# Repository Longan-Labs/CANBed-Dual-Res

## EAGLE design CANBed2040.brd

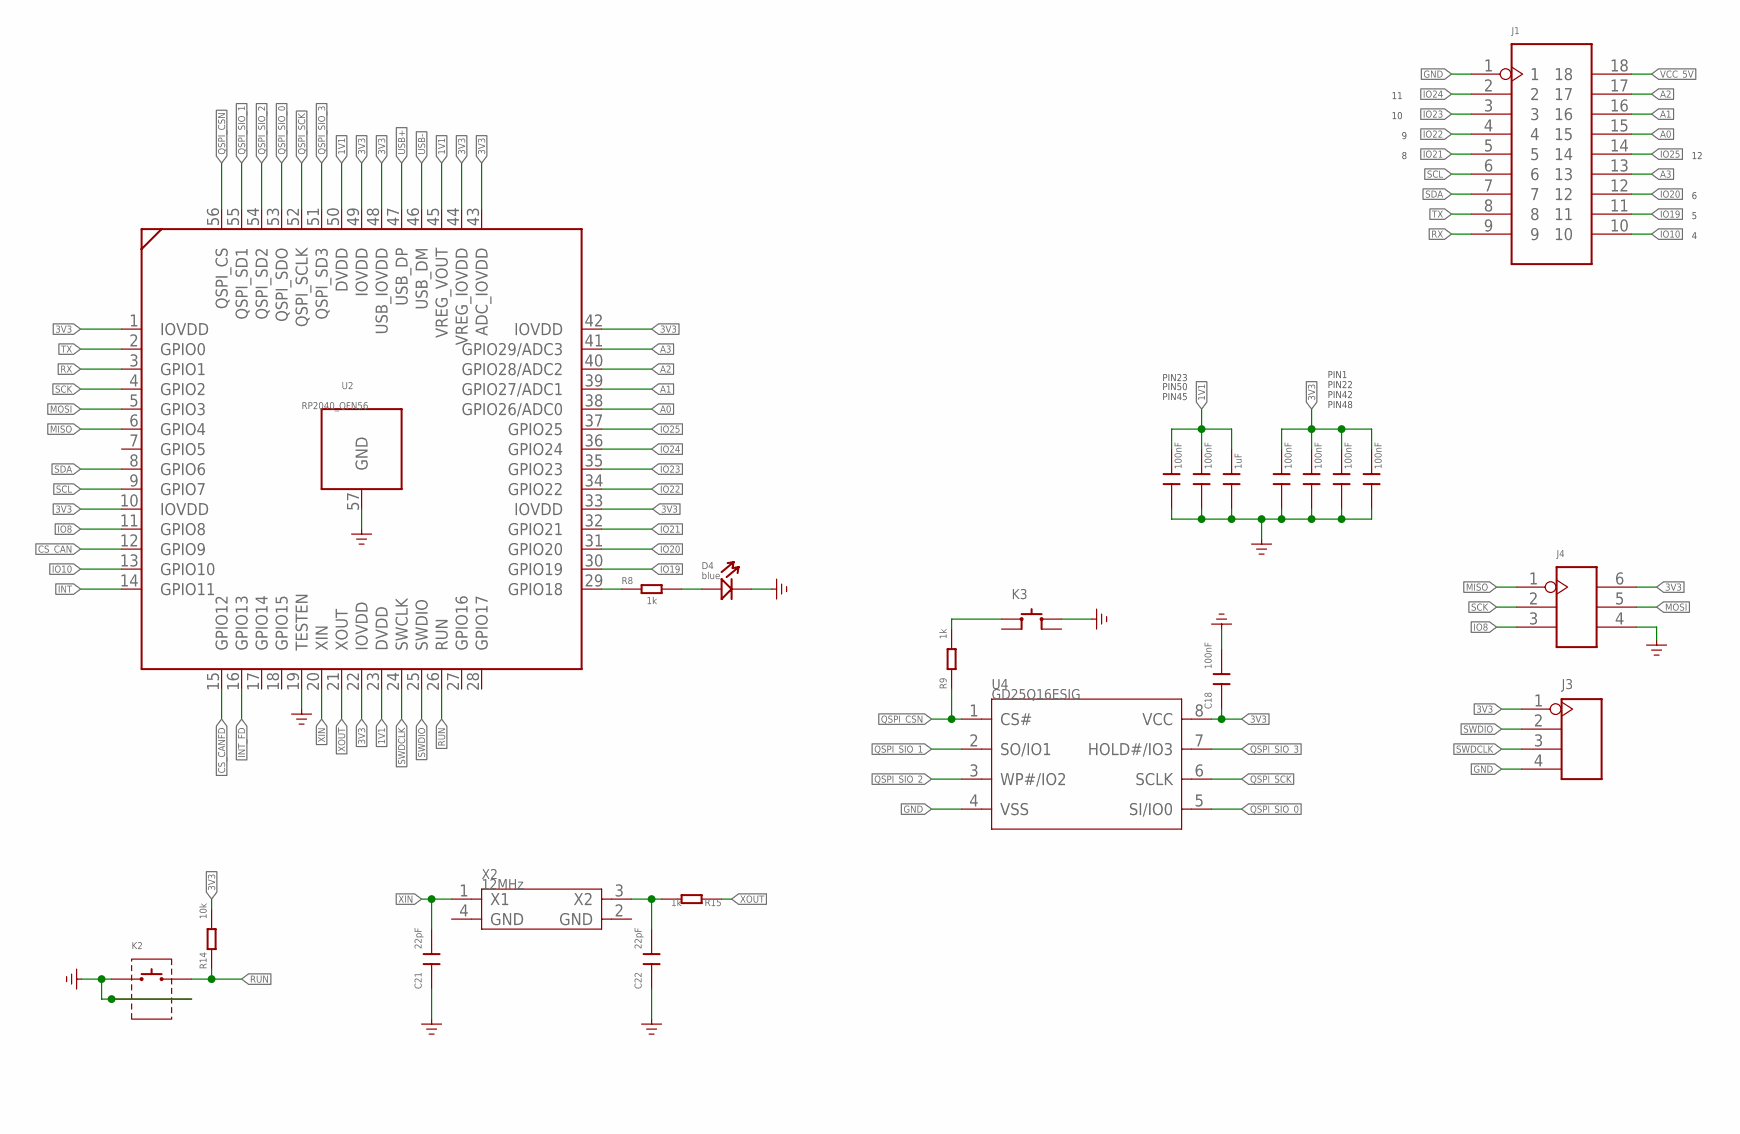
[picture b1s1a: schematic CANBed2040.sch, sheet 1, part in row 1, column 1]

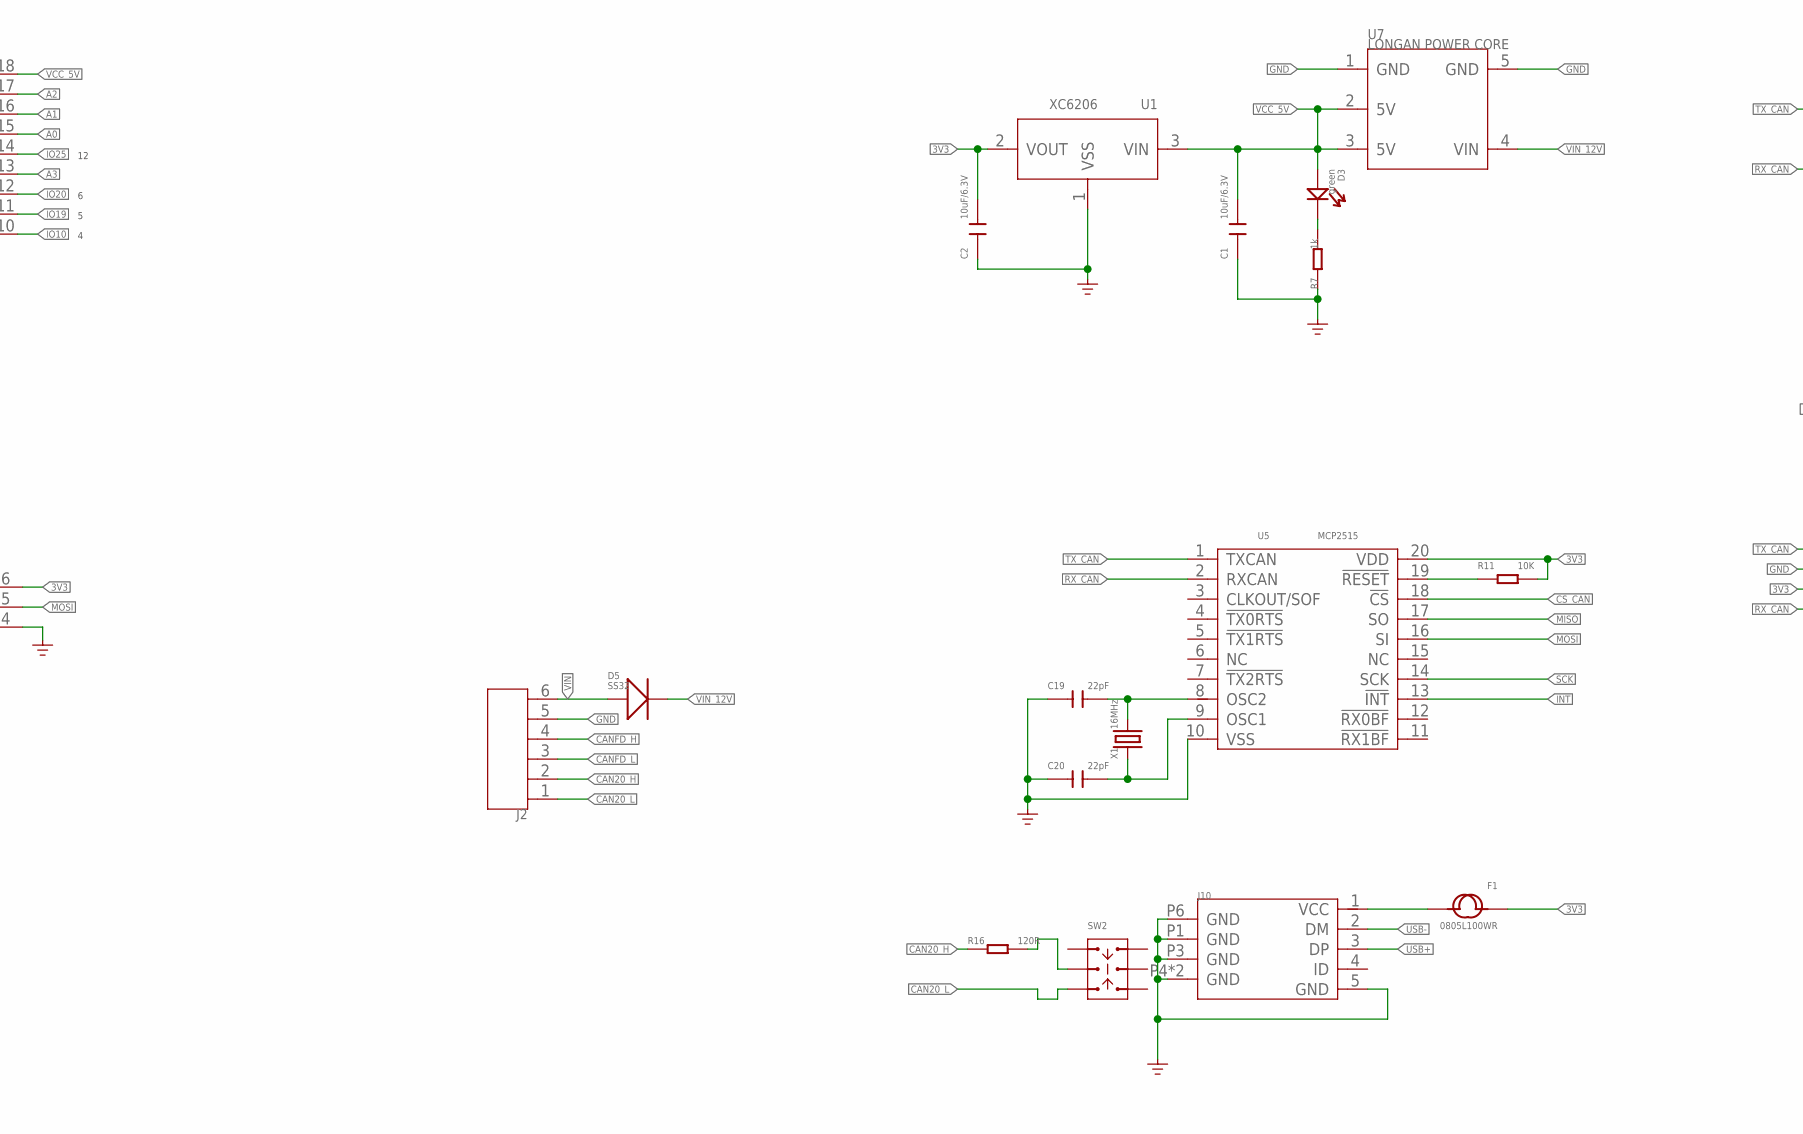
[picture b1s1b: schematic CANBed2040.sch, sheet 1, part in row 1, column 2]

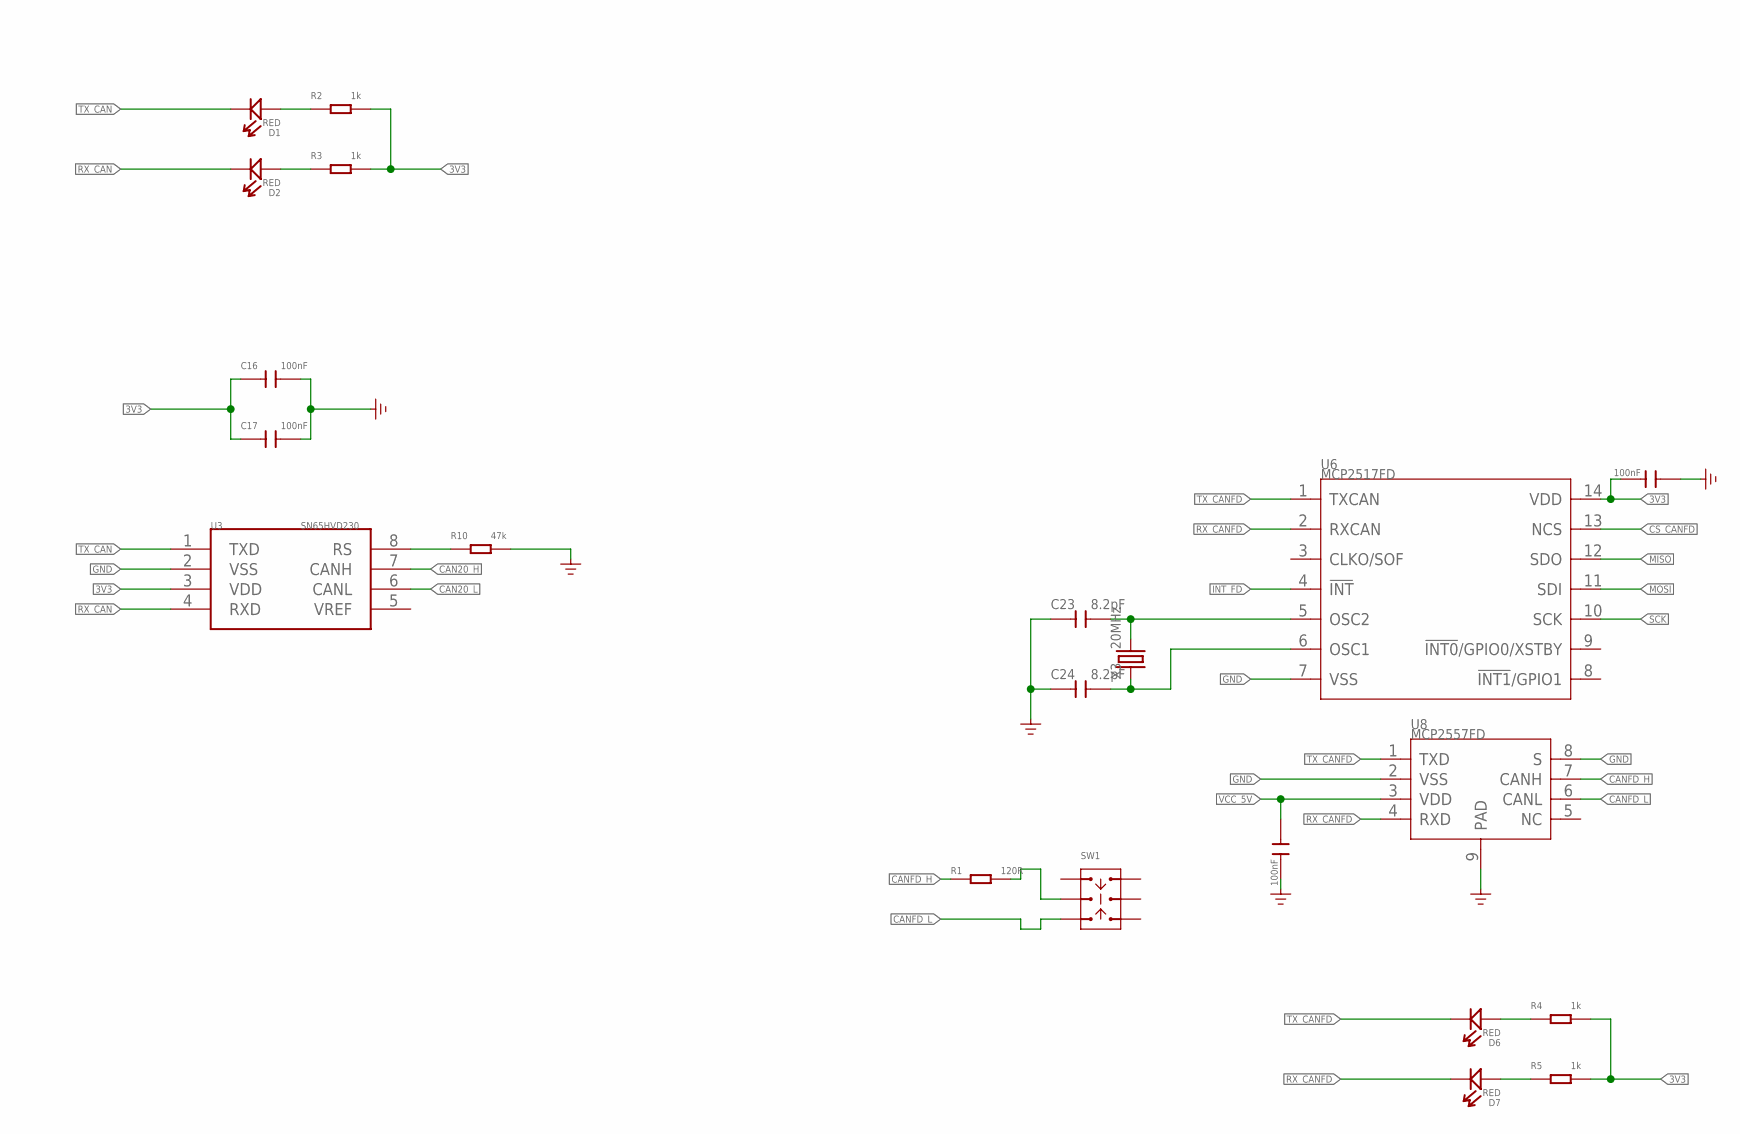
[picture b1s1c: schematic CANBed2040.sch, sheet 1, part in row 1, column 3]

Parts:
C1, C2: 10uF/6.3V; C0603
C9, C10, C12, C13, C14, C15, C16, C17, C18, C25, C26: 100nF; C0603
C11: 1uF; C0603
C19, C20, C21, C22: 22pF; C0603
C23, C24: 8.2pF; C0603
D1, D2, D6, D7: RED; LED-0603
D3: green; LED-0603
D4: blue; LED-0603
D5: SS32; DO-214AC
F1: 0805L100WR; F0805
J1: HEADER-2X9P-2.54; H2X9-2.54
J2: SCREW-TERMINAL-6P-3.5; H6-3.5-21.7X7.0MM
J3: HEADER-4P-SMD; H4-SMD-2.54
J4: HEADER-2X3P-2.54; H2X3-2.54
J10: MICRO-USB5+4P-320010050; MICRO-USB5+5P-SMD-0.65-7.2X5.06MM
K2: BUTTON-2+2P; SW2+2P-7.7X2.75X3.95MM
K3: BUTTON-4P-4.5X4.5X3.3MM; SW4-4.5X4.5X3.3MM
R1, R16: 120R; R0603
R2, R3, R4, R5, R7, R8, R9, R15: 1k; R0603
R10: 47k; R0603
R11: 10K; R0603
R14: 10k; R0603
SW1, SW2: SWITCH-2CH-6P-311010004; SW6-2.54-9.0X3.5X3.2+2.0MM
U1: XC6206; SOT-23
U2: RP2040_QFN56
U3: SN65HVD230; SOIC8-6.0
U4: GD25Q16ESIG; SOP8-1.27-5.3X5.25X2MM
U5: MCP2515; TSSOP20-0.65-6.5X4.4MM
U6: MCP2517FD; SOIC14-1.27-8.6X3.9MM
U7: LONGAN POWER CORE; MOUDLE5P-2.54-19X12MM
U8: MCP2557FD; TDFN8-0.5-2X3X0.75MM
X1: 16MHz; X4-SMD-3.2X2.5X0.7MM
X2: 12MHz; X4-SMD-3.2X2.5X0.7MM
X3: 20MHz; X4-SMD-3.2X2.5X0.7MM

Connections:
1V1: C9.2, C10.2, C11.2, U2.23 (DVDD), U2.45 (VREG_VOUT), U2.50 (DVDD)
3V3: C2.2, C12.2, C13.2, C14.2, C15.2, C16.1, C17.1, C18.1, C25.2, F1.1, J3.1, J4.6, R2.2, R3.2, R4.2, R5.2, R11.2, R14.2, U1.2 (VOUT), U2.1 (IOVDD), U2.10 (IOVDD), U2.22 (IOVDD), U2.33 (IOVDD), U2.42 (IOVDD), U2.43 (ADC_IOVDD), U2.44 (VREG_IOVDD), U2.48 (USB_IOVDD), U2.49 (IOVDD), U3.3 (VDD), U4.8 (VCC), U5.20 (VDD), U6.14 (VDD)
A0: J1.15, U2.38 (GPIO26/ADC0)
A1: J1.16, U2.39 (GPIO27/ADC1)
A2: J1.17, U2.40 (GPIO28/ADC2)
A3: J1.13, U2.41 (GPIO29/ADC3)
CAN20_H: J2.2, R16.1, U3.7 (CANH)
CAN20_L: J2.1, SW2.CH1B, U3.6 (CANL)
CANFD_H: J2.4, R1.1, U8.7 (CANH)
CANFD_L: J2.3, SW1.CH1B, U8.6 (CANL)
CS_CAN: U2.12 (GPIO9), U5.18 (!CS)
CS_CANFD: U2.15 (GPIO12), U6.13 (NCS)
EXT_PWR: F1.2, J10.1 (VCC)
GND: C1.1, C2.1, C9.1, C10.1, C11.1, C12.1, C13.1, C14.1, C15.1, C16.2, C17.2, C18.2, C19.1, C20.1, C21.1, C22.1, C23.1, C24.1, C25.1, C26.2, D4.-, J1.1, J2.5, J3.4, J4.4, J10.5 (GND), J10.P1 (GND), J10.P3 (GND), J10.P4 (GND), J10.P5 (GND), J10.P6 (GND), K2.1, K2.S1, K2.S2, K3.3 (B0), R7.1, R10.2, U1.1 (VSS), U2.19 (TESTEN), U2.57 (GND), U3.2 (VSS), U4.4 (VSS), U5.10 (VSS), U6.7 (VSS), U7.1 (GND), U7.5 (GND), U8.2 (VSS), U8.8 (S), U8.9 (PAD)
INT: U2.14 (GPIO11), U5.13 (!INT)
INT_FD: U2.16 (GPIO13), U6.4 (!INT)
IO8: J4.3, U2.11 (GPIO8)
IO10: J1.10, U2.13 (GPIO10)
IO19: J1.11, U2.30 (GPIO19)
IO20: J1.12, U2.31 (GPIO20)
IO21: J1.5, U2.32 (GPIO21)
IO22: J1.4, U2.34 (GPIO22)
IO23: J1.3, U2.35 (GPIO23)
IO24: J1.2, U2.36 (GPIO24)
IO25: J1.14, U2.37 (GPIO25)
MISO: J4.1, U2.6 (GPIO4), U5.17 (SO), U6.12 (SDO)
MOSI: J4.5, U2.5 (GPIO3), U5.16 (SI), U6.11 (SDI)
unnamed: D3.-, R7.2
unnamed: D1.+, R2.1
unnamed: R8.1, U2.29 (GPIO18)
unnamed: R1.2, SW1.COM1
unnamed: R16.2, SW2.COM1
unnamed: D4.+, R8.2
unnamed: K3.1 (A0), R9.2
unnamed: C22.2, R15.2, X2.3 (X2)
unnamed: D6.+, R4.1
unnamed: D7.+, R5.1
unnamed: C23.2, U6.5 (OSC2), X3.3 (2)
unnamed: C24.2, U6.6 (OSC1), X3.1
unnamed: D2.+, R3.1
unnamed: C19.2, U5.8 (OSC2), X1.3 (2)
unnamed: C20.2, U5.9 (OSC1), X1.1
unnamed: R10.1, U3.8 (RS)
QSPI_CSN: R9.1, U2.56 (QSPI_CS), U4.1 (CS#)
QSPI_SCK: U2.52 (QSPI_SCLK), U4.6 (SCLK)
QSPI_SIO_0: U2.53 (QSPI_SDO), U4.5 (SI/IO0)
QSPI_SIO_1: U2.55 (QSPI_SD1), U4.2 (SO/IO1)
QSPI_SIO_2: U2.54 (QSPI_SD2), U4.3 (WP#/IO2)
QSPI_SIO_3: U2.51 (QSPI_SD3), U4.7 (HOLD#/IO3)
RST_N: R11.1, U5.19 (!RESET)
RUN: K2.2, R14.1, U2.26 (RUN)
RX: J1.9, U2.3 (GPIO1)
RX_CAN: D2.-, U3.4 (RXD), U5.2 (RXCAN)
RX_CANFD: D7.-, U6.2 (RXCAN), U8.4 (RXD)
SCK: J4.2, U2.4 (GPIO2), U5.14 (SCK), U6.10 (SCK)
SCL: J1.6, U2.9 (GPIO7)
SDA: J1.7, U2.8 (GPIO6)
SWDCLK: J3.3, U2.24 (SWCLK)
SWDIO: J3.2, U2.25 (SWDIO)
TX: J1.8, U2.2 (GPIO0)
TX_CAN: D1.-, U3.1 (TXD), U5.1 (TXCAN)
TX_CANFD: D6.-, U6.1 (TXCAN), U8.1 (TXD)
USB+: J10.3 (DP), U2.47 (USB_DP)
USB-: J10.2 (DM), U2.46 (USB_DM)
VCC_5V: C1.2, C26.1, D3.+, J1.18, U1.3 (VIN), U7.2 (5V), U7.3 (5V), U8.3 (VDD)
VIN: D5.1 (+), J2.6
VIN_12V: D5.2 (-), U7.4 (VIN)
XIN: C21.2, U2.20 (XIN), X2.1 (X1)
XOUT: R15.1, U2.21 (XOUT)

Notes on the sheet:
PIN1
PIN22
PIN42
PIN48
PIN23
PIN50
PIN45

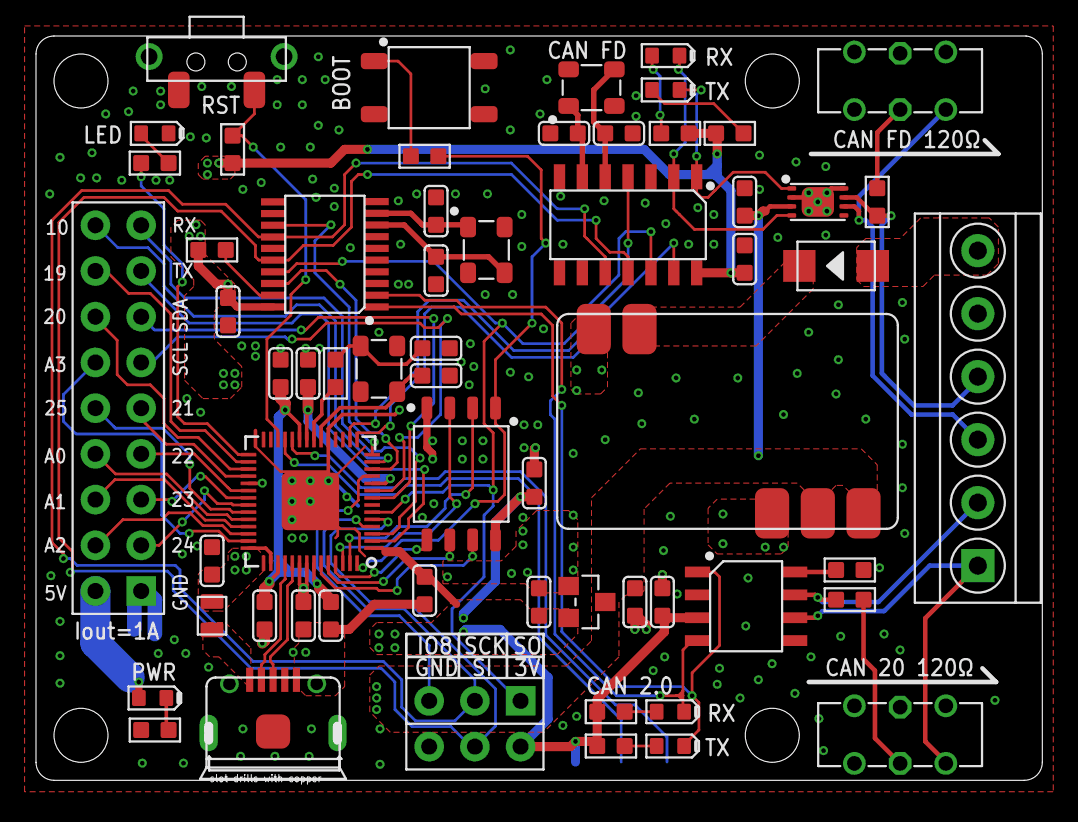
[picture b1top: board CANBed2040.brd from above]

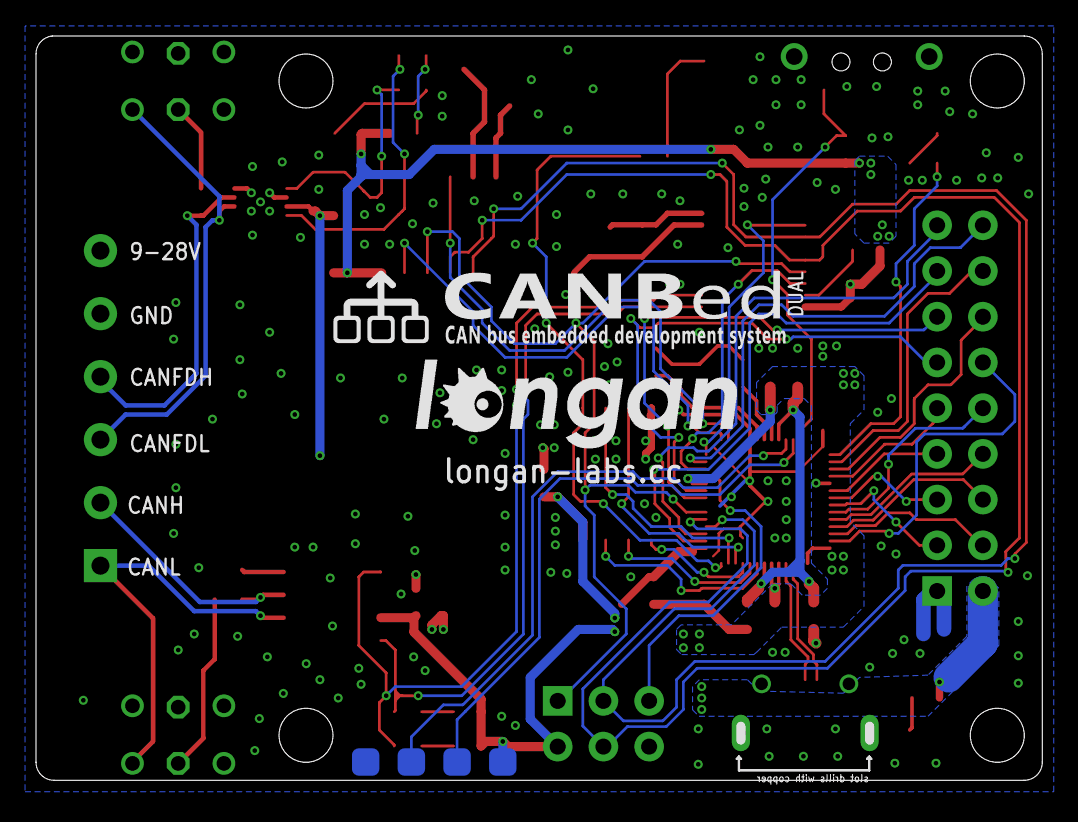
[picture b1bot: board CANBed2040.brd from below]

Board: 2 copper layers, 55.9 x 41.4 mm, 62 parts (2 on the bottom side), 69 nets.

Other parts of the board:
U$12: LONGAN-SILK-SMALL

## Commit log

2021-12-08 create
